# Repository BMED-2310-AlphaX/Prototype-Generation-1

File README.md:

# AlphaX — Prototype Generation 1

Non-pharmacological anxiety management device. BMED 2310 Junior Design, Team AlphaX.

Transcutaneous vagus nerve stimulation with adjustable treatment intensity,
controlled from a mobile app over Bluetooth Low Energy.

## Why adjustable intensity

PRN medication commits the user to a dose chosen before they know how bad an
episode will be. Onset is delayed, the dose can't be reduced once taken, and
repeated use carries dependency risk.

AlphaX inverts that. The user starts low, feels the effect in seconds, and
adjusts either direction continuously. A dose that's too strong is corrected in
about a second instead of metabolized over hours.

## Repository layout

```
ios-app/
  AlphaX/        13 Swift source files — drag into a new Xcode iOS App project
  SETUP.md       step-by-step build and test guide

firmware/
  alphax_tvns_ble/     MAIN BUILD — stim engine + Bluetooth control
  esp32_standalone/    Bluetooth only, no stimulation (bring-up / demo)
  esp32_howland_dctest/DC bench test into a dummy load
  esp32_ble_bridge/    ESP32 as radio, paired with the STM32
  stm32_session_controller/  Nucleo-F303RE session logic
  uno_bench_demo/      Arduino Uno, no radio
  nano_session_controller/   Arduino Nano, no radio

bridge/          USB fallback — browser UI when no BLE radio is available
docs/
```

Circuit files (LTspice, STM32 CubeIDE project) live in their own folders at the
repository root.

## Main build

`firmware/alphax_tvns_ble/` merges two pieces of work:

| File | Author |
|---|---|
| `stim.cpp`, `stim.h` | Max — biphasic stimulation engine, unchanged |
| `alphax_tvns_ble.ino` | Joy — BLE service and session logic |
| `WIRING.txt` | Max |

The stimulation engine owns the waveform, amplitude ramp, parameter limits,
e-stop and timer watchdog. The BLE layer adds a radio and a session clock on
top. Nothing in the BLE layer touches the DAC directly — every output change
goes through `stim_set()` / `stim_start()` / `stim_stop()`, so the engine's
safety checks cannot be bypassed by a command from the phone.

Put all three files in one folder named `alphax_tvns_ble` (Arduino requires the
folder name to match the `.ino`), board **DOIT ESP32 DEVKIT V1**, core
**esp32 by Espressif 3.x**.

## Stimulation parameters

| | |
|---|---|
| Waveform | biphasic, charge-balanced |
| Amplitude | 5 mA at the app's 80% ceiling |
| Pulse width | 250 µs per phase |
| Interphase gap | 50 µs |
| Frequency | 25 Hz (40 ms period, 39.45 ms rest) |
| Resolution | 8-bit DAC, ~129 µA per step |

Simulated charge imbalance is 0.06% of one phase's charge at 5 mA.

## Wiring

| ESP32 | Goes to |
|---|---|
| GPIO25 (DAC1) | free end of R3 — Howland `vin` |
| GPIO26 (DAC2) | free end of R1, **lifted off ground** — Howland `vref` |
| GND | battery midpoint |
| 100 kΩ | across GPIO25 and GPIO26 |
| GPIO27 | analog-side enable, optional |

Driving R1 instead of grounding it makes the Howland input differential, so
`Iout ∝ (GPIO25 − GPIO26)`. That produces a bipolar command from two unipolar
DACs with no level-shifting stage.

**Never connect ±9 V to the ESP32.** Power it from USB. Order: USB in and
booted → batteries on → `on`. Shut down in reverse.

## Architecture

```
  iPhone  ──BLE──►  ESP32  ──DAC──►  Howland current pump  ──►  electrodes
   app              firmware            analog stage
```

**The device owns all session state and every safety limit.** The phone issues
commands and displays status; it never runs the session clock. Closing the app
mid-session doesn't interrupt treatment, and a crashed or disconnected phone
cannot produce an unsafe output.

## BLE protocol

Service `6E5A0001-B5A3-F393-E0A9-E50E24DCCA9E`

| Characteristic | UUID | Direction | Payload |
|---|---|---|---|
| Command | `…0002` | write | `START:<intensity>:<minutes>` · `STOP` · `SET:<intensity>` |
| Status | `…0003` | notify | JSON at 2 Hz |

```json
{"state":"running","intensity":40,"target":40,"remaining":1183,
 "bpm":0.0,"rmssd":0.0,"batt":255,"amp_uA":2452}
```

`amp_uA` is measured amplitude after ramp and DAC rounding, not the commanded
value. Commands are plain text, so the firmware can be driven from a serial
terminal with no app involved.

`BLEDevice::setMTU(247)` must be called before `BLEDevice::init()` — the
23-byte default truncates the telemetry packet.

## Two interfaces

Patients see a breathing pacer and session controls. Heart rate and HRV are
restricted to a clinician view reached by a non-obvious gesture.

This is deliberate. Evidence on wearable heart-rate monitoring in anxious
populations indicates that continuous cardiac display can reinforce the
symptom-monitoring behaviour the device is meant to interrupt.

## Status

| | |
|---|---|
| iOS app | complete, verified on hardware |
| BLE link | firmware written, bring-up in progress |
| Stimulation engine | written, simulated, bench test pending |
| Analog stage | built, waveform verified on scope |
| HRV sensing | implemented in firmware, no sensor yet |

## Known issues

- **Compliance margin at 5 mA.** Simulation gives `Vmax` = 8.14 V against ±9 V
  rails. Test at 2 mA first and watch for current droop at the pulse tail.
- **Current leakage** identified in Thread 1 bench testing; bleed resistor to
  ground before electrode 1 is the proposed fix.
- **Design Inputs Worksheet** still specifies a cranial electrotherapy
  predicate (Alpha-Stim AID, 0–500 µA, 0.5 Hz, ear clips). The built device is
  tVNS at 5 mA, 25 Hz, neck electrodes. EA-2 current density and EA-3 timing
  need redoing against the actual parameters.

## Safety

- Amplitude and duration limits enforced in firmware, not in the app
- Amplitude ramps rather than stepping
- Output stops automatically if the Bluetooth link drops
- BOOT button is a hardware e-stop
- Task watchdog and stimulation-timer watchdog both force output to zero on stall

**Test into a resistive dummy load first:**

```
drv ──[ 10k ∥ 470nF ]──[ 500Ω ]──[ 10k ∥ 470nF ]── GND
```

Scope the current through the 500 Ω and confirm charge balance before any
electrode touches skin. Instructor review required before human contact.

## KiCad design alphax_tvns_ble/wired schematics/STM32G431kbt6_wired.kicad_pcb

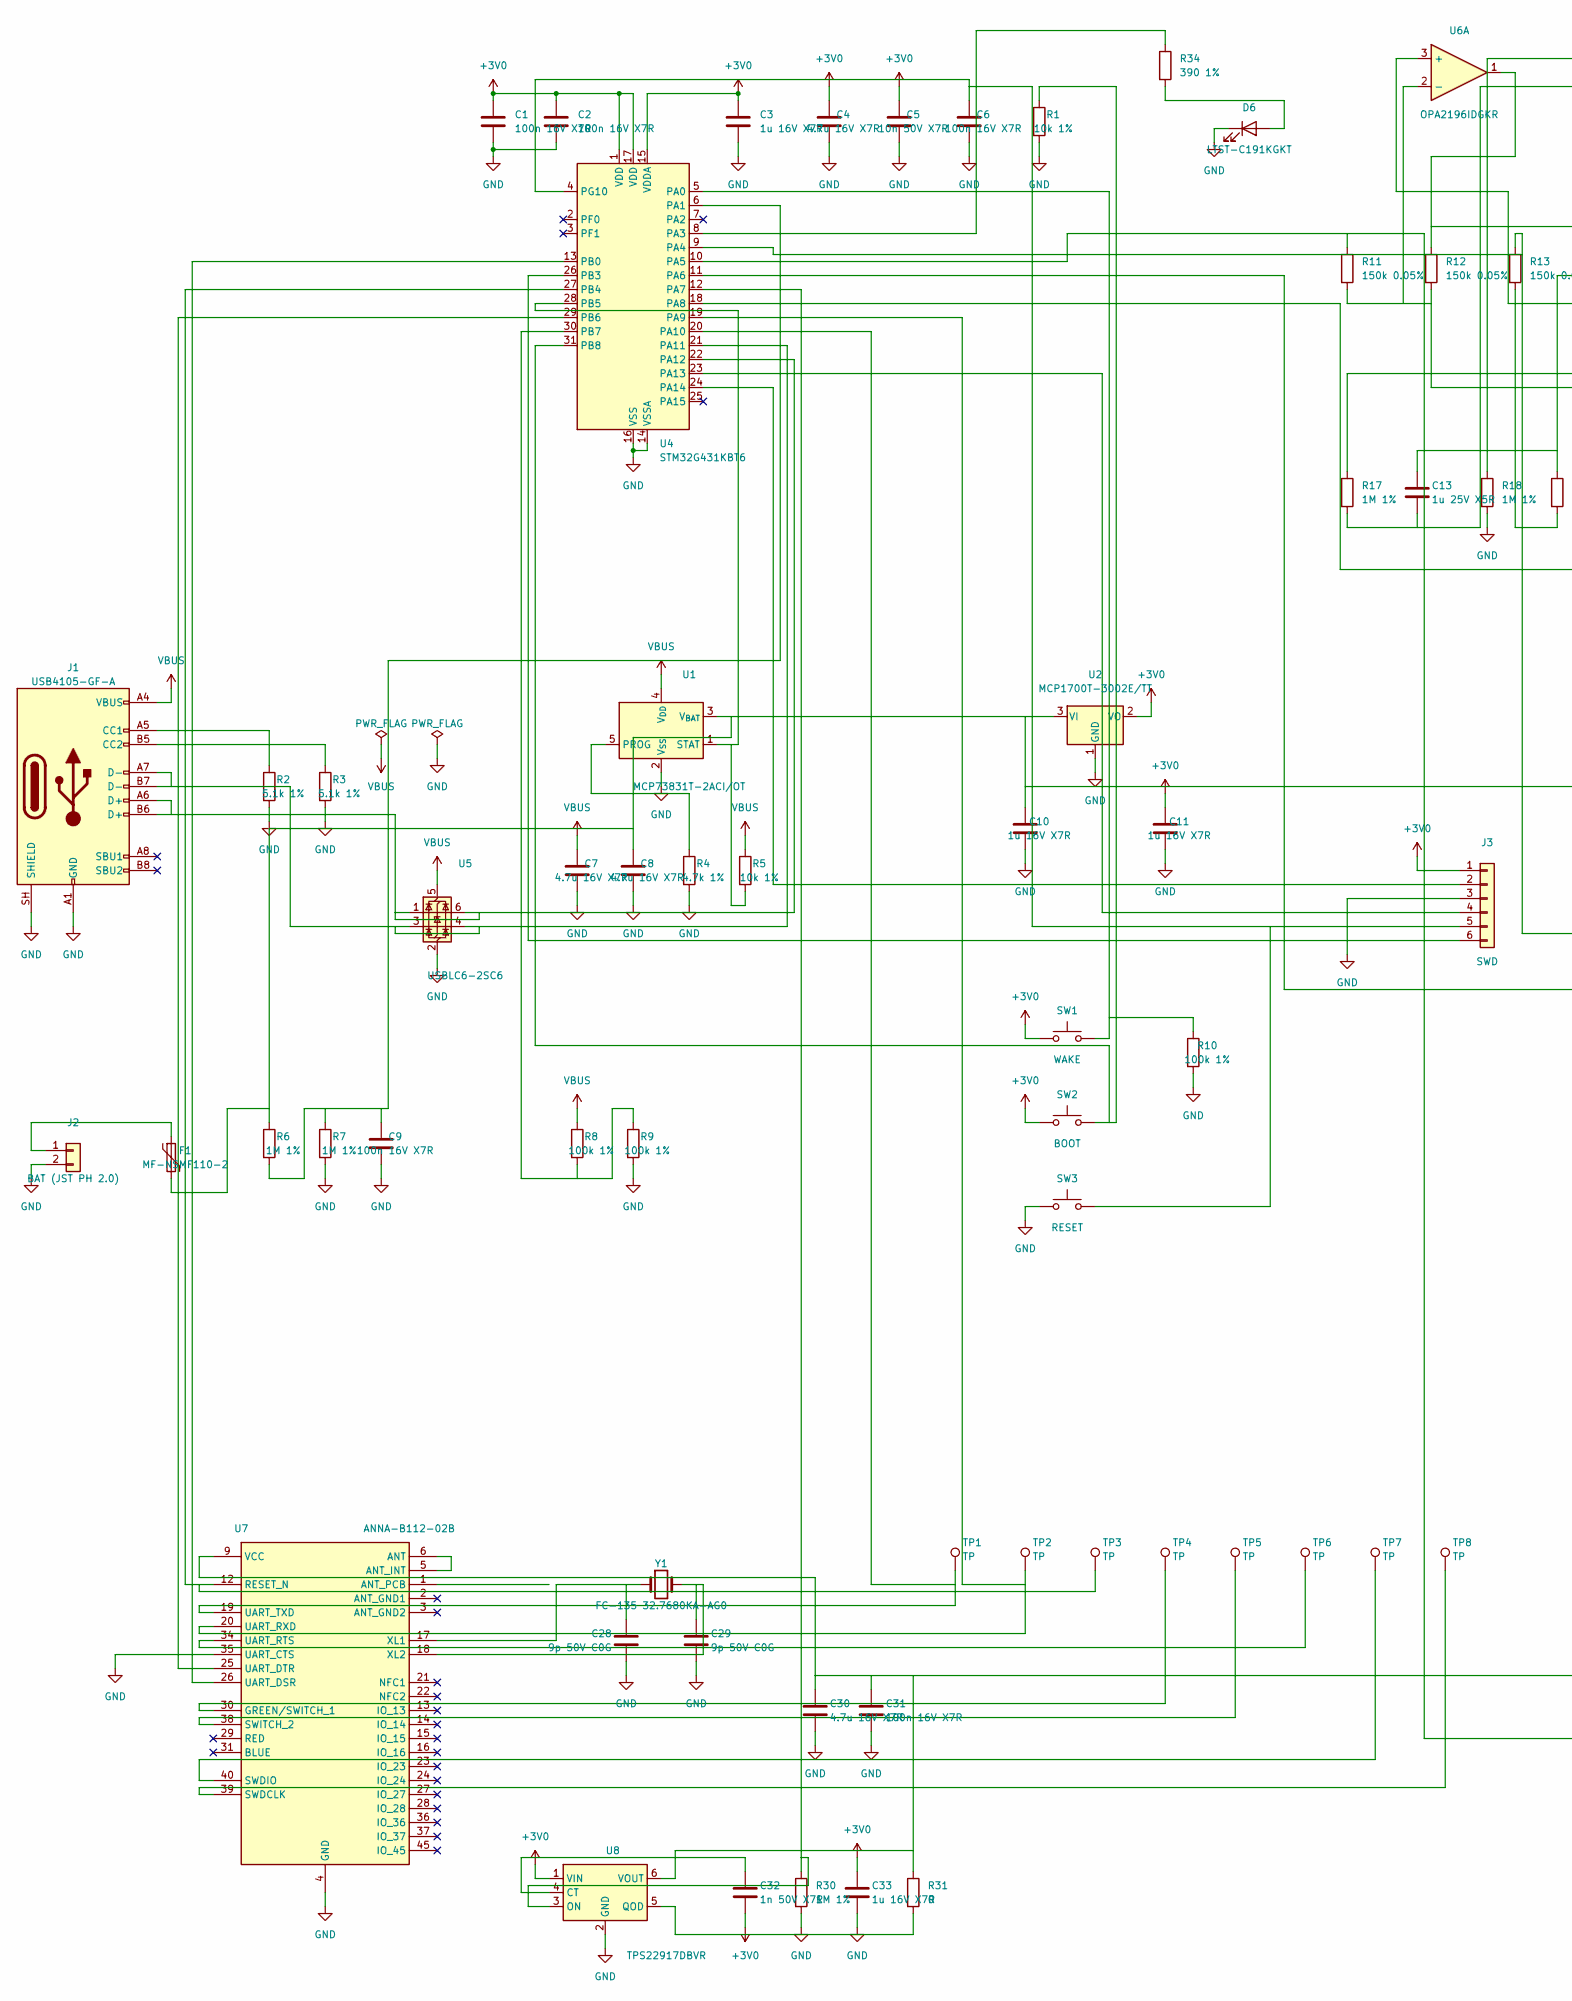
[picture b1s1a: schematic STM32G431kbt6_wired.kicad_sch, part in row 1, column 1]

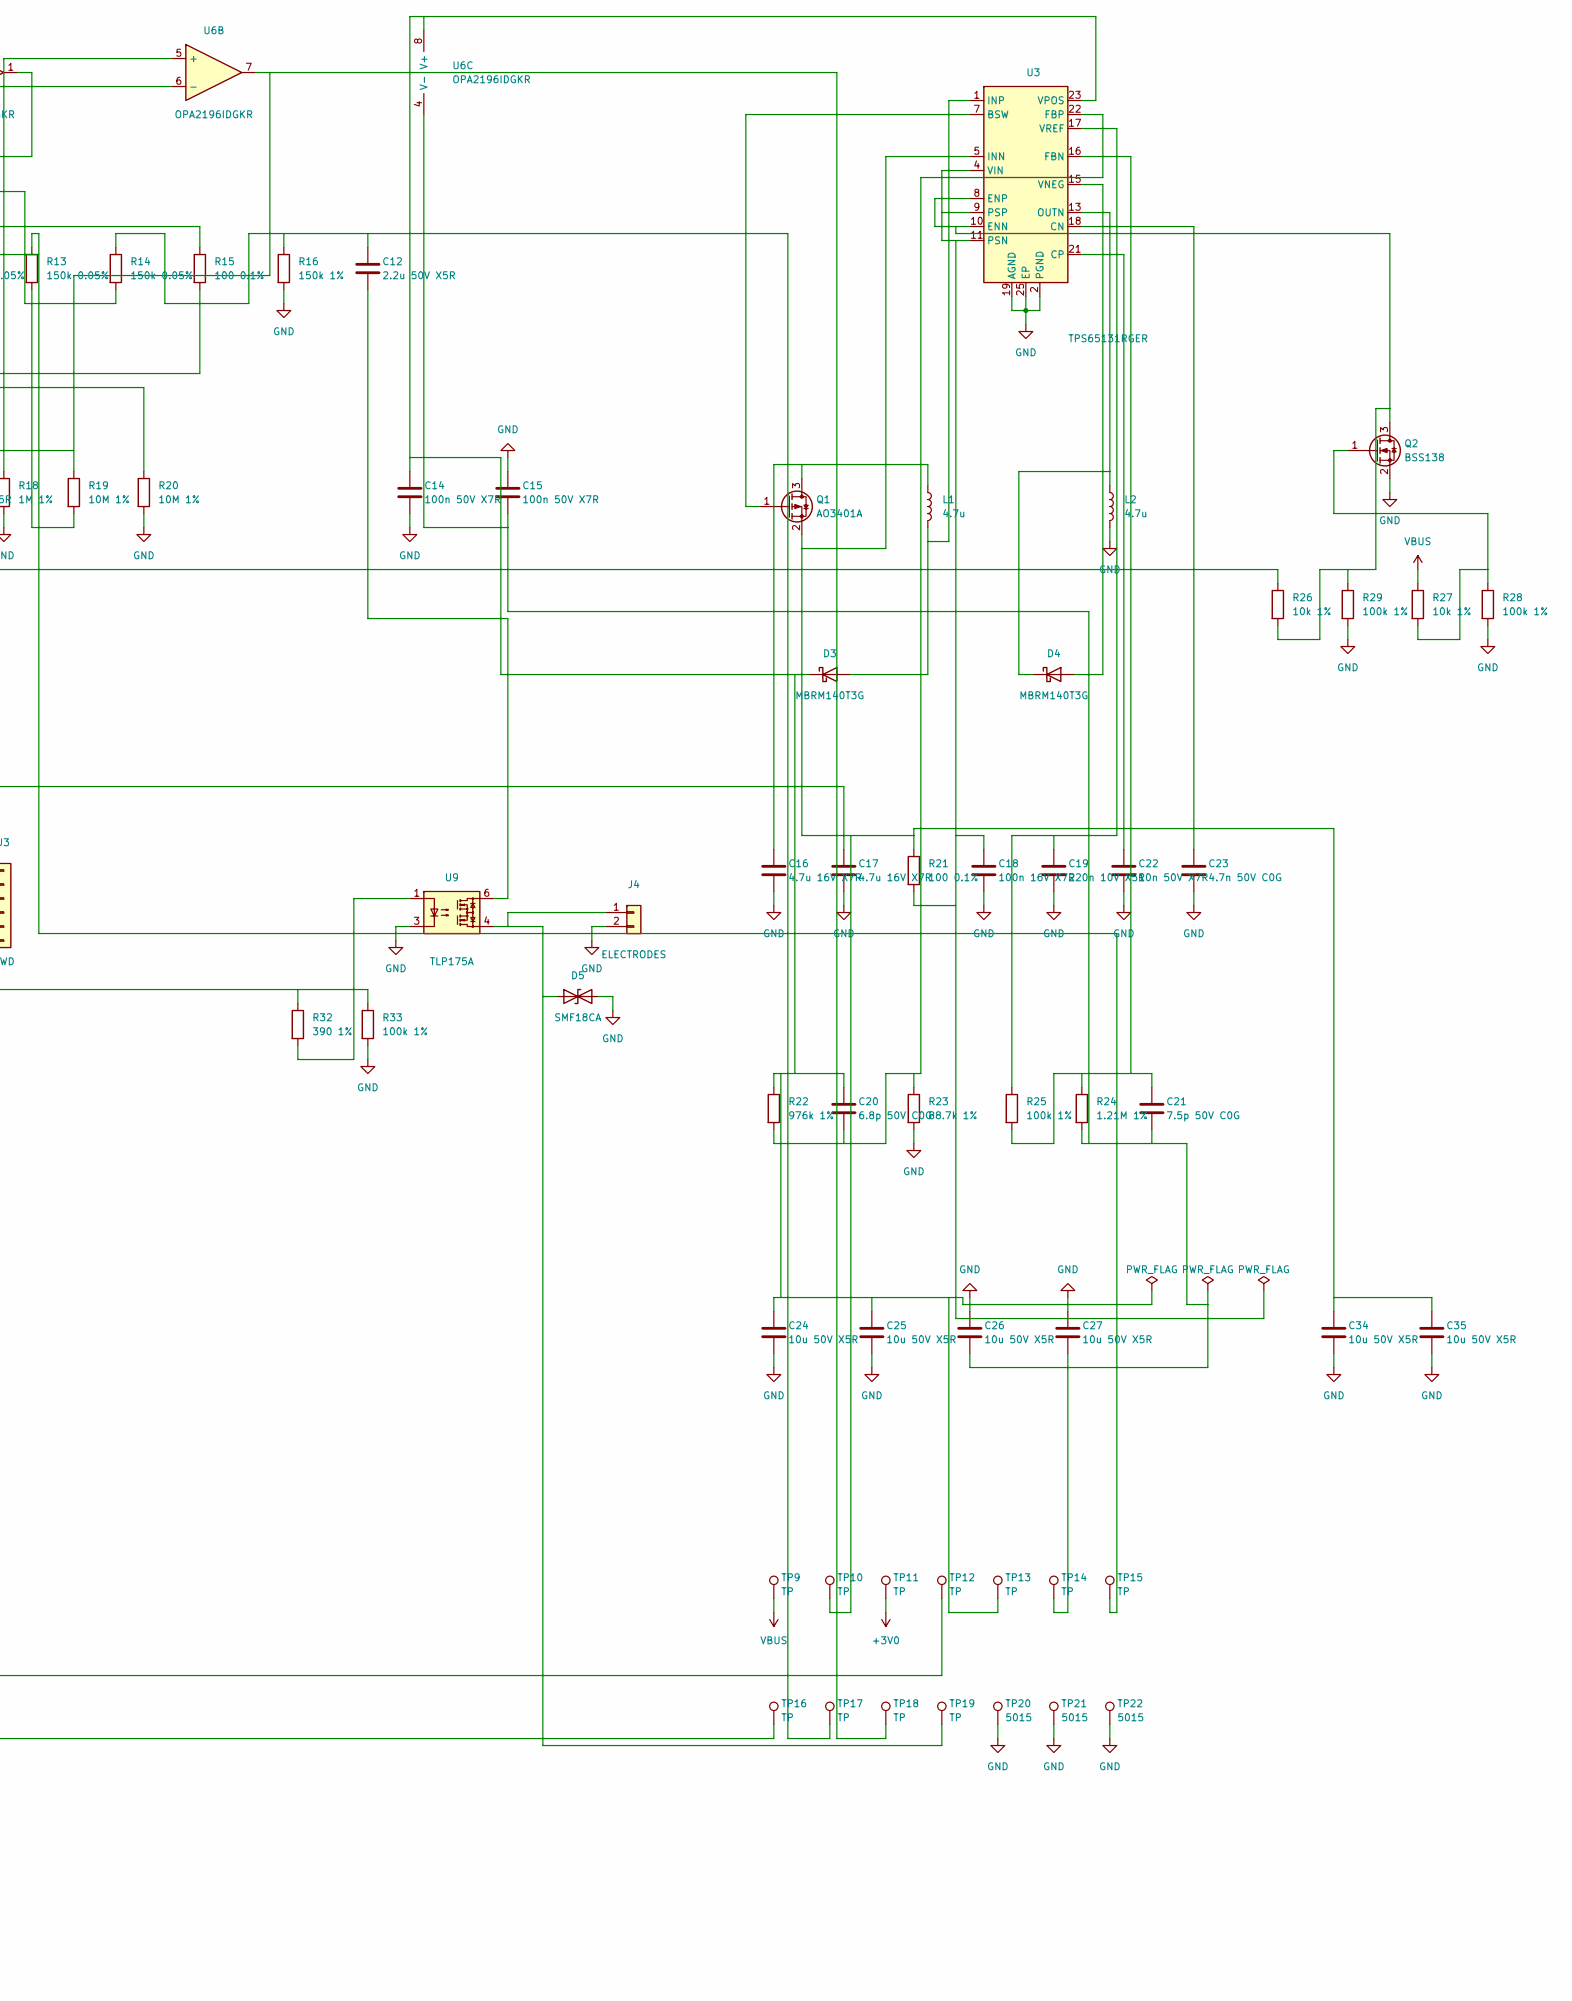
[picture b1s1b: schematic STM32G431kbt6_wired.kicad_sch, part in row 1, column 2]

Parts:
C1, C2, C6, C9, C18, C31: 100n 16V X7R; C_0603_1608Metric; MPN C0603C104M4RACTU
C3, C10, C11, C33: 1u 16V X7R; C_0603_1608Metric; MPN EMK107B7105KA-T
C4, C7, C8, C16, C17, C30: 4.7u 16V X7R; C_0805_2012Metric; MPN GRM21BR71C475KE51L
C5, C22: 10n 50V X7R; C_0402_1005Metric; MPN CL05B103KB5NNNC
C12: 2.2u 50V X5R; C_0603_1608Metric; MPN GRT188R61H225KE13D
C13: 1u 25V X5R; C_0402_1005Metric; MPN C0402B105K025T
C14, C15: 100n 50V X7R; C_0402_1005Metric; MPN GCM155R71H104KE02J
C19: 220n 10V X5R; C_0402_1005Metric; MPN GRM155R61A224KE19D
C20: 6.8p 50V C0G; C_0402_1005Metric; MPN KGM05ACG1H6R8CH
C21: 7.5p 50V C0G; C_0402_1005Metric; MPN CC0402CRNPO9BN7R5
C23: 4.7n 50V C0G; C_0402_1005Metric; MPN GRM1555C1H472JE01D
C24, C25, C26, C27, C34, C35: 10u 50V X5R; C_1206_3216Metric; MPN UMK316BBJ106ML-T
C28, C29: 9p 50V C0G; C_0402_1005Metric; MPN CC0402CRNPO9BN9R0
C32: 1n 50V X7R; C_0402_1005Metric; MPN C0402C102K5RACTU
D3, D4: MBRM140T3G; D_Powermite_LargeCathode; MPN MBRM140T3G; DigiKey MBRM140T3GOSCT-ND
D5: SMF18CA; D_SOD-123F; MPN SMF18CA
D6: LTST-C191KGKT; LED_0603_1608Metric; MPN LTST-C191KGKT; DigiKey 160-1446-1-ND
F1: MF-NSMF110-2; Fuse_1206_3216Metric; MPN MF-NSMF110-2
J1: USB4105-GF-A; USB_C_Receptacle_GCT_USB4105-xx-A_16P_TopMnt_Horizontal; MPN USB4105-GF-A
J2: BAT (JST PH 2.0); JST_PH_S2B-PH-SM4-TB_1x02-1MP_P2.00mm_Horizontal; MPN S2B-PH-SM4-TB(LF)(SN)
J3: SWD; PinHeader_2x03_P2.54mm_Vertical_SMD; MPN PHED-SS006G1ABONE-B300
J4: ELECTRODES; SolderWire-0.25sqmm_1x02_P4.2mm_D0.65mm_OD1.7mm_Relief
L1, L2: 4.7u; L_TDK_TFM252012; MPN TFM252012ALMA4R7MTAA
Q1: AO3401A; SOT-23; MPN AO3401A
Q2: BSS138; SOT-23; MPN BSS138; DigiKey BSS138CT-ND
R1, R5, R26, R27: 10k 1%; R_0603_1608Metric; MPN RNCP0603FTD10K0
R2, R3: 5.1k 1%; R_0603_1608Metric; MPN RT0603FRE075K1L
R4: 4.7k 1%; R_0603_1608Metric; MPN RT0603FRE074K7L
R6, R7, R17, R18, R30: 1M 1%; R_0603_1608Metric; MPN MCT06030C1004FPW00
R8, R9, R10, R25, R28, R29, R33: 100k 1%; R_0805_2012Metric; MPN RT0805FRD07100KL
R11, R12, R13, R14: 150k 0.05%; R_0603_1608Metric; MPN RG1608N-154-W-T1; DigiKey RG16N150KWCT-ND
R15, R21: 100 0.1%; R_0603_1608Metric; MPN RG1608P-101-B-T5; DigiKey RG16P100BCT-ND
R16: 150k 1%; R_0603_1608Metric; MPN ERJ-3EKF1503V
R19, R20: 10M 1%; R_0402_1005Metric; MPN RMCF0402FT10M0
R22: 976k 1%; R_0603_1608Metric; MPN CR0603-FX-9763ELF
R23: 88.7k 1%; R_0603_1608Metric; MPN CR0603-FX-8872ELF
R24: 1.21M 1%; R_0603_1608Metric; MPN RM06F1214CT
R31: 0; R_0603_1608Metric; MPN MCT0603MZ0000ZP500
R32, R34: 390 1%; R_0603_1608Metric; MPN RT0603FRE07390RL
SW1: WAKE; SW_SPST_PTS810; MPN PTS810 SJM 250 SMTR LFS
SW2: BOOT; SW_SPST_PTS810; MPN PTS810 SJM 250 SMTR LFS
SW3: RESET; SW_SPST_PTS810; MPN PTS810 SJM 250 SMTR LFS
TP1, TP2, TP3, TP4, TP5, TP6, TP7, TP8: TP; TestPoint_Pad_1.0x1.0mm
TP9, TP10, TP11, TP12, TP13, TP14, TP15, TP16, TP17, TP18, TP19: TP; TestPoint_Pad_D1.5mm
TP20, TP21, TP22: 5015; TestPoint_Keystone_5015_Micro_Mini; MPN 5015
U1: MCP73831T-2ACI/OT; SOT-23-5; MPN MCP73831T-2ACI/OT
U2: MCP1700T-3002E/TT; SOT-23; MPN MCP1700T-3002E/TT
U3: TPS65131RGER; VQFN-24-1EP_4x4mm_P0.5mm_EP2.45x2.45mm_ThermalVias; MPN TPS65131RGER
U4: STM32G431KBT6; LQFP-32_7x7mm_P0.8mm; MPN STM32G431KBT6
U5: USBLC6-2SC6; SOT-23-6; MPN USBLC6-2SC6
U6: OPA2196IDGKR; VSSOP-8_3x3mm_P0.65mm; MPN OPA2196IDGKR
U7: ANNA-B112-02B; u-blox_ANNA-B112; MPN ANNA-B112-02B
U8: TPS22917DBVR; SOT-23-6; MPN TPS22917DBVR
U9: TLP175A; Toshiba_SOIC-4-6_4.4x3.6mm_P1.27mm; MPN TLP175A(TPL,E
Y1: FC-135 32.7680KA-AG0; Crystal_SMD_3215-2Pin_3.2x1.5mm; MPN FC-135 32.7680KA-AG0; DigiKey 114-FC-13532.7680KA-AG0CT-ND

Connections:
+3V0: C1.1, C2.1, C3.1, C4.1, C5.1, C11.1, C32.2, C33.1, J3.1, SW1.1, SW2.1, TP11.1 (1_1), U2.2 (VO), U4.1 (VDD), U4.15 (VDDA), U4.17 (VDD), U8.1 (VIN)
GND: C1.2, C2.2, C3.2, C4.2, C5.2, C6.2, C7.2, C8.2, C9.2, C10.2, C11.2, C14.2, C15.1, C16.2, C17.2, C18.2, C19.2, C22.2, C23.2, C24.2, C25.2, C26.1, C27.1, C28.2, C29.2, C30.2, C31.2, C33.2, C34.2, C35.2, D5.2 (A2), D6.1 (K), J1.A1 (GND), J1.A12 (GND), J1.B1 (GND), J1.B12 (GND), J1.SH (SHIELD), J2.2, J3.3, J4.2, L2.2, Q2.2 (S), R1.2, R2.2, R3.2, R4.2, R7.2, R9.2, R10.2, R16.2, R18.2, R20.2, R23.2, R28.2, R29.2, R30.2, R33.2, SW3.1 (1_1), TP20.1 (1_1), TP21.1 (1_1), TP22.1 (1_1), U1.2 (V_{SS}), U2.1 (GND), U3.2 (PGND), U3.3 (PGND), U3.19 (AGND), U3.25 (EP), U4.14 (VSSA), U4.16 (VSS), U4.32 (VSS), U5.2 (GND), U7.4 (GND), U7.7 (GND), U7.8 (GND), U7.10 (GND), U7.11 (GND), U7.32 (GND), U7.33 (GND), U7.35 (UART_CTS), U7.41 (GND), U7.42 (GND), U7.43 (GND), U7.44 (GND), U7.46 (GND), U7.47 (GND), U7.48 (GND), U7.49 (GND), U7.50 (GND), U7.51 (GND), U7.52 (GND), U8.2 (GND), U9.3; also elsewhere on the board
unnamed: C12.1, R14.1, R15.2, R16.1, R17.1, TP17.1 (1_1)
unnamed: C12.2, U9.6
unnamed: C20.1, R22.1
unnamed: C21.1, R24.1, R25.2
unnamed: C21.2, C26.2, C27.2, R24.2, TP14.1 (1_1)
unnamed: C24.1, C25.1
unnamed: D3.2 (A), L1.2, U3.1 (INP), U3.24 (INP)
unnamed: C14.1, D3.1 (K), U3.23 (VPOS), U6.8 (V+)
unnamed: C15.2, D4.2 (A), U3.15 (VNEG), U6.4 (V-)
unnamed: D4.1 (K), L2.1, U3.13 (OUTN), U3.14 (OUTN)
unnamed: D5.1 (A1), J4.1, TP19.1 (1_1), U9.4
unnamed: D6.2 (A), R34.2
unnamed: F1.2, R6.1
unnamed: J1.A5 (CC1), R2.1
unnamed: J1.B5 (CC2), R3.1
unnamed: F1.1, J2.1
unnamed: J3.2, U4.24 (PA14)
unnamed: J3.4, U4.23 (PA13)
unnamed: C6.1, J3.5, U4.4 (PG10)
unnamed: J3.6, U4.26 (PB3)
unnamed: C16.1, L1.1, Q1.3 (D)
unnamed: Q1.1 (G), U3.7 (BSW)
unnamed: C17.1, C34.1, C35.1, Q1.2 (S), R21.1, U3.5 (INN), U3.6 (INN)
unnamed: Q2.3 (D), R26.2, R29.1, U3.8 (ENP), U3.10 (ENN)
unnamed: Q2.1 (G), R27.2, R28.1
unnamed: R11.2, R12.2, R20.1
unnamed: R12.1, U6.1
unnamed: R13.1, TP15.1 (1_1)
unnamed: R19.1, TP18.1 (1_1), U6.7
unnamed: R32.2, U9.1
unnamed: R4.1, U1.5 (PROG)
unnamed: R5.2, U1.1 (STAT), U4.28 (PB5)
unnamed: C8.1, U1.3 (V_{BAT}), U2.3 (VI)
unnamed: C23.1, U3.18 (CN)
unnamed: C22.1, U3.21 (CP)
unnamed: C20.2, R22.2, R23.1, U3.22 (FBP)
unnamed: U3.4 (VIN), U3.9 (PSP), U3.11 (PSN)
unnamed: C19.1, R25.1, U3.17 (VREF)
unnamed: SW1.2, U4.5 (PA0)
unnamed: C9.1, R6.2, R7.1, U4.6 (PA1)
unnamed: R34.1, U4.8 (PA3)
unnamed: R11.1, TP16.1 (1_1), U4.10 (PA5)
unnamed: R32.1, R33.1, U4.11 (PA6)
unnamed: R30.1, U4.12 (PA7), U8.3 (ON)
unnamed: R26.1, U4.18 (PA8)
unnamed: TP2.1 (1_1), U4.19 (PA9), U7.20 (UART_RXD)
unnamed: TP1.1 (1_1), U4.20 (PA10), U7.19 (UART_TXD)
unnamed: J1.A7 (D-), J1.B7 (D-), U4.21 (PA11), U5.3 (I/O2), U5.4 (I/O2)
unnamed: J1.A6 (D+), J1.B6 (D+), U4.22 (PA12), U5.1 (I/O1), U5.6 (I/O1)
unnamed: U4.13 (PB0), U7.26 (UART_DSR)
unnamed: TP3.1 (1_1), U4.27 (PB4), U7.12 (RESET_N)
unnamed: U4.29 (PB6), U7.25 (UART_DTR)
unnamed: R8.2, R9.1, U4.30 (PB7)
unnamed: R1.1, SW2.2, U4.31 (PB8)
unnamed: R13.2, R14.2, R19.2, U6.3 (+)
unnamed: R18.1, U6.5 (+)
unnamed: C13.2, R17.2, U6.6 (-)
unnamed: U7.5 (ANT_INT), U7.6 (ANT)
unnamed: TP4.1 (1_1), U7.30 (GREEN/SWITCH_1)
unnamed: TP8.1 (1_1), U7.39 (SWDCLK)
unnamed: TP7.1 (1_1), U7.40 (SWDIO)
unnamed: TP5.1 (1_1), U7.38 (SWITCH_2)
unnamed: TP6.1 (1_1), U7.34 (UART_RTS)
unnamed: C30.1, C31.1, TP12.1 (1_1), U7.9 (VCC)
unnamed: C28.1, U7.17 (XL1), Y1.1
unnamed: C29.1, U7.18 (XL2), Y1.2
unnamed: C32.1, U8.4 (CT)
unnamed: R31.2, U8.5 (QOD)
VBUS: C7.1, J1.A4 (VBUS), J1.A9 (VBUS), J1.B4 (VBUS), J1.B9 (VBUS), R5.1, R8.1, R27.1, TP9.1 (1_1), U1.4 (V_{DD}), U5.5 (VBUS)

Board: 4 copper layers, 118 parts (0 on the bottom side), 71 nets, no tracks yet.

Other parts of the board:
NT1: NetTie_2; NetTie-2_SMD_Pad0.5mm

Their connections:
GND: NT1.2; also elsewhere on the board

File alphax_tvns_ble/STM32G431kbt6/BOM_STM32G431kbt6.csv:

"AlphaX next-gen board (STM32G431KB) - BOM for ONE device, generated from STM32G431kbt6.kicad_sch"

PARTS TO BUY
Item,Qty,References,Value,Description,MPN,DigiKey PN,Footprint,Notes
1,1,U1,MCP73831T-2ACI/OT,"Single cell Li-ion/Li-Po charge controller, 4.20 V",MCP73831T-2ACI/OT,,SOT-23-5,
2,1,U2,MCP1700T-3002E/TT,"250mA Low Quiescent Current LDO, 3.0V output, SOT-23",MCP1700T-3002E/TT,,SOT-23,
3,1,U3,TPS65131RGER,"Positive and negative output DC-DC converter, 1.95 A switch, VQFN-24",TPS65131RGER,,VQFN-24-1EP_4x4mm_P0.5mm_EP2.45x2.45mm_ThermalVias,
4,1,U4,STM32G431KBT6,"STMicroelectronics Arm Cortex-M4 MCU, 128KB flash, 32KB RAM, 170 MHz, 1.71-3.6V, 26 GPIO, LQFP32",STM32G431KBT6,,LQFP-32_7x7mm_P0.8mm,Order STM32G431KBT6 (-40 to 85 C)
5,1,U5,USBLC6-2SC6,"Very low capacitance ESD protection diode, 2 data-line, SOT-23-6",USBLC6-2SC6,,SOT-23-6,
6,1,U6,OPA2196IDGKR,"Dual 36 V low-power rail-to-rail op amp, VSSOP-8",OPA2196IDGKR,,VSSOP-8_3x3mm_P0.65mm,
7,1,U7,ANNA-B112-02B,"u-blox Bluetooth LE 5 SiP module (nRF52832), internal antenna",ANNA-B112-02B,,u-blox_ANNA-B112,Ships with u-connectXpress firmware; custom footprint AlphaX:u-blox_ANNA-B112
8,1,U8,TPS22917DBVR,"1V to 5.5V, 2A, 80mOhm ultra-low leakage load switch, SOT23-6",TPS22917DBVR,,SOT-23-6,
9,1,U9,TLP175A,"MOSFET photorelay 1-Form-A, Voff 60 V, Ion 100 mA, SOIC-4-6 (MFSOP-4-6)","TLP175A(TPL,E",,Toshiba_SOIC-4-6_4.4x3.6mm_P1.27mm,Toshiba TLP175A (4-pin SO6)
10,1,Q1,AO3401A,"P-MOSFET transistor, gate/source/drain",AO3401A,,SOT-23,
11,1,Q2,BSS138,"50V Vds, 0.22A Id, N-Channel MOSFET, SOT-23",BSS138,BSS138CT-ND,SOT-23,
12,2,D3 D4,MBRM140T3G,Schottky diode,MBRM140T3G,MBRM140T3GOSCT-ND,D_Powermite_LargeCathode,Check pad 1 = cathode (large tab) vs onsemi case 457-04
13,1,D5,SMF18CA,"Bidirectional TVS, 18 V standoff, 200 W, SOD-123FL",SMF18CA,,D_SOD-123F,"Slkor (Shenzhen Slkormicro) SMF18CA, bidirectional, SOD-123FL; Littelfuse SMF18CA is the equivalent"
14,1,D6,LTST-C191KGKT,"Green 0603 LED, 571 nm",LTST-C191KGKT,160-1446-1-ND,LED_0603_1608Metric,
15,2,L1 L2,4.7u,Inductor,TFM252012ALMA4R7MTAA,,L_TDK_TFM252012,Custom footprint AlphaX:L_TDK_TFM252012 (TDK land pattern)
16,1,Y1,FC-135 32.7680KA-AG0,Two pin crystal,FC-135 32.7680KA-AG0,114-FC-13532.7680KA-AG0CT-ND,Crystal_SMD_3215-2Pin_3.2x1.5mm,
17,1,F1,MF-NSMF110-2,"Resettable fuse, polymeric positive temperature coefficient",MF-NSMF110-2,,Fuse_1206_3216Metric,
18,4,R1 R5 R26 R27,10k 1%,Resistor,RNCP0603FTD10K0,,R_0603_1608Metric,
19,2,R2 R3,5.1k 1%,Resistor,RT0603FRE075K1L,,R_0603_1608Metric,
20,1,R4,4.7k 1%,Resistor,RT0603FRE074K7L,,R_0603_1608Metric,
21,5,R6 R7 R17 R18 R30,1M 1%,Resistor,MCT06030C1004FPW00,,R_0603_1608Metric,
22,7,R8 R9 R10 R25 R28 R29 R33,100k 1%,Resistor,RT0805FRD07100KL,,R_0805_2012Metric,
23,4,R11 R12 R13 R14,150k 0.05%,Resistor,RG1608N-154-W-T1,RG16N150KWCT-ND,R_0603_1608Metric,Matched Howland bridge resistors (0.05%)
24,2,R15 R21,100 0.1%,Resistor,RG1608P-101-B-T5,RG16P100BCT-ND,R_0603_1608Metric,
25,1,R16,150k 1%,Resistor,ERJ-3EKF1503V,,R_0603_1608Metric,Rbleed; ordinary 1% is enough
26,2,R19 R20,10M 1%,Resistor,RMCF0402FT10M0,,R_0402_1005Metric,
27,1,R22,976k 1%,Resistor,CR0603-FX-9763ELF,,R_0603_1608Metric,
28,1,R23,88.7k 1%,Resistor,CR0603-FX-8872ELF,,R_0603_1608Metric,
29,1,R24,1.21M 1%,Resistor,RM06F1214CT,,R_0603_1608Metric,
30,1,R31,0,Resistor,MCT0603MZ0000ZP500,,R_0603_1608Metric,
31,2,R32 R34,390 1%,Resistor,RT0603FRE07390RL,,R_0603_1608Metric,
32,6,C1 C2 C6 C9 C18 C31,100n 16V X7R,Unpolarized capacitor,C0603C104M4RACTU,,C_0603_1608Metric,
33,4,C3 C10 C11 C33,1u 16V X7R,Unpolarized capacitor,EMK107B7105KA-T,,C_0603_1608Metric,
34,6,C4 C7 C8 C16 C17 C30,4.7u 16V X7R,Unpolarized capacitor,GRM21BR71C475KE51L,,C_0805_2012Metric,
35,2,C5 C22,10n 50V X7R,Unpolarized capacitor,CL05B103KB5NNNC,,C_0402_1005Metric,
36,1,C12,2.2u 50V X5R,Unpolarized capacitor,GRT188R61H225KE13D,,C_0603_1608Metric,Cblock (keeps DC off the electrodes)
37,1,C13,1u 25V X5R,Unpolarized capacitor,C0402B105K025T,,C_0402_1005Metric,
38,2,C14 C15,100n 50V X7R,Unpolarized capacitor,GCM155R71H104KE02J,,C_0402_1005Metric,
39,1,C19,220n 10V X5R,Unpolarized capacitor,GRM155R61A224KE19D,,C_0402_1005Metric,
40,1,C20,6.8p 50V C0G,Unpolarized capacitor,KGM05ACG1H6R8CH,,C_0402_1005Metric,
41,1,C21,7.5p 50V C0G,Unpolarized capacitor,CC0402CRNPO9BN7R5,,C_0402_1005Metric,
42,1,C23,4.7n 50V C0G,Unpolarized capacitor,GRM1555C1H472JE01D,,C_0402_1005Metric,
43,6,C24 C25 C26 C27 C34 C35,10u 50V X5R,Unpolarized capacitor,UMK316BBJ106ML-T,,C_1206_3216Metric,
44,2,C28 C29,9p 50V C0G,Unpolarized capacitor,CC0402CRNPO9BN9R0,,C_0402_1005Metric,
45,1,C32,1n 50V X7R,Unpolarized capacitor,C0402C102K5RACTU,,C_0402_1005Metric,
46,1,J1,USB4105-GF-A,USB 2.0-only 16P Type-C Receptacle,USB4105-GF-A,,USB_C_Receptacle_GCT_USB4105-xx-A_16P_TopMnt_Horizontal,
47,1,J2,BAT (JST PH 2.0),"Generic connector, single row, 01x02",S2B-PH-SM4-TB(LF)(SN),,JST_PH_S2B-PH-SM4-TB_1x02-1MP_P2.00mm_Horizontal,
48,1,J3,SWD,"Generic connector, single row, 01x06",PHED-SS006G1ABONE-B300,,PinHeader_2x03_P2.54mm_Vertical_SMD,2x3 2.54 mm SMD; SWD to Nucleo ST-LINK CN4
49,3,SW1 SW2 SW3,WAKE / BOOT / RESET,"Push button switch, generic, two pins",PTS810 SJM 250 SMTR LFS,,SW_SPST_PTS810,
50,3,TP20 TP21 TP22,5015,test point,5015,,TestPoint_Keystone_5015_Micro_Mini,

OFF-BOARD ITEMS (not in the schematic)
Item,Qty,References,Value,Description,MPN,DigiKey PN,Footprint,Notes
51,1,BT1,500 mAh LiPo,Protected Li-polymer cell with JST PH lead (plugs into J2),Adafruit 1578,,,Check lead polarity against J2 pin 1 before plugging in
52,2,,Electrode + lead,"Custom-fabricated electrodes, soldered to J4 pads",,,,Up to 0.25 mm2 / 24 AWG lead

PCB COPPER ONLY (nothing to buy)
Item,Qty,References,Value,Description,MPN,DigiKey PN,Footprint,Notes
-1,1,J4,ELECTRODES,Solder pads with strain relief for the electrode leads,,,SolderWire-0.25sqmm_1x02_P4.2mm_D0.65mm_OD1.7mm_Relief,
-2,8,TP1 TP2 TP3 TP4 TP5 TP6 TP7 TP8,TP,test point,,,TestPoint_Pad_1.0x1.0mm,
-3,11,TP9 TP10 TP11 TP12 TP13 TP14 TP15 TP16 TP17 TP18 TP19,TP,test point,,,TestPoint_Pad_D1.5mm,
-4,1,NT1,NetTie_2,"Net tie, 2 pins",,,NetTie-2_SMD_Pad0.5mm,

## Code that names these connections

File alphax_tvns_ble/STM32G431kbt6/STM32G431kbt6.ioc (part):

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Mcu.Name=STM32G431K(6-8-B)Tx
Mcu.Package=LQFP32
Mcu.UserName=STM32G431KBTx
PA0.GPIOParameters=GPIO_Label,GPIO_ModeDefaultEXTI
PA0.GPIO_Label=WAKE
PA0.GPIO_ModeDefaultEXTI=GPIO_MODE_IT_RISING
PA0.Signal=GPXTI0
PA1.GPIOParameters=GPIO_Label
PA1.GPIO_Label=VBAT_SENSE
PA1.Mode=IN2-Single-Ended
PA1.Signal=ADC1_IN2
PA10.GPIOParameters=GPIO_Label
PA10.GPIO_Label=BLE_TXD
PA10.Mode=Asynchronous
PA10.Signal=USART1_RX
PA11.GPIOParameters=GPIO_Label
PA11.GPIO_Label=USB_DM
PA11.Mode=Device
PA11.Signal=USB_DM
PA12.GPIOParameters=GPIO_Label
PA12.GPIO_Label=USB_DP
PA12.Mode=Device
PA12.Signal=USB_DP
PA13.GPIOParameters=GPIO_Label
PA13.GPIO_Label=SWDIO
PA13.Mode=Trace_Asynchronous_SW
PA13.Signal=SYS_JTMS-SWDIO
PA14.GPIOParameters=GPIO_Label
PA14.GPIO_Label=SWCLK
PA14.Mode=Trace_Asynchronous_SW
PA14.Signal=SYS_JTCK-SWCLK
PA3.GPIOParameters=GPIO_Label
PA3.GPIO_Label=STATUS_LED
PA3.Signal=GPIO_Output
PA4.GPIOParameters=GPIO_Label
PA4.GPIO_Label=DAC_STIM
PA4.Signal=COMP_DAC11_group
PA5.GPIOParameters=GPIO_Label
PA5.GPIO_Label=DAC_REF
PA5.Signal=COMP_DAC12_group
PA6.GPIOParameters=GPIO_Label
PA6.GPIO_Label=OUT_EN
PA6.Signal=GPIO_Output
PA7.GPIOParameters=GPIO_Label
PA7.GPIO_Label=BLE_EN
PA7.Signal=GPIO_Output
PA8.GPIOParameters=GPIO_Label
PA8.GPIO_Label=EN_RAIL_MCU
PA8.Signal=GPIO_Output
PA9.GPIOParameters=GPIO_Label
PA9.GPIO_Label=BLE_RXD
PA9.Mode=Asynchronous
PA9.Signal=USART1_TX
PB0.GPIOParameters=GPIO_Label
PB0.GPIO_Label=BLE_DSR
PB0.Signal=GPIO_Output
PB3.GPIOParameters=GPIO_Label
PB3.GPIO_Label=SWO
PB3.Mode=Trace_Asynchronous_SW
PB3.Signal=SYS_JTDO-SWO
PB4.GPIOParameters=GPIO_Label,GPIO_ModeDefaultOutputPP
PB4.GPIO_Label=BLE_RESET_N
PB4.GPIO_ModeDefaultOutputPP=GPIO_MODE_OUTPUT_OD
PB4.Signal=GPIO_Output
PB5.GPIOParameters=GPIO_Label
PB5.GPIO_Label=STAT
PB5.Signal=GPIO_Input
PB6.GPIOParameters=GPIO_PuPd,GPIO_Label
PB6.GPIO_Label=BLE_DTR
PB6.GPIO_PuPd=GPIO_PULLDOWN
PB6.Signal=GPIO_Input
PB7.GPIOParameters=GPIO_Label,GPIO_ModeDefaultEXTI
PB7.GPIO_Label=VBUS_SENSE
PB7.GPIO_ModeDefaultEXTI=GPIO_MODE_IT_RISING_FALLING
PB7.Signal=GPXTI7
RCC.HSE_VALUE=8000000
RCC.SYSCLKFreq_VALUE=16000000
board=custom
